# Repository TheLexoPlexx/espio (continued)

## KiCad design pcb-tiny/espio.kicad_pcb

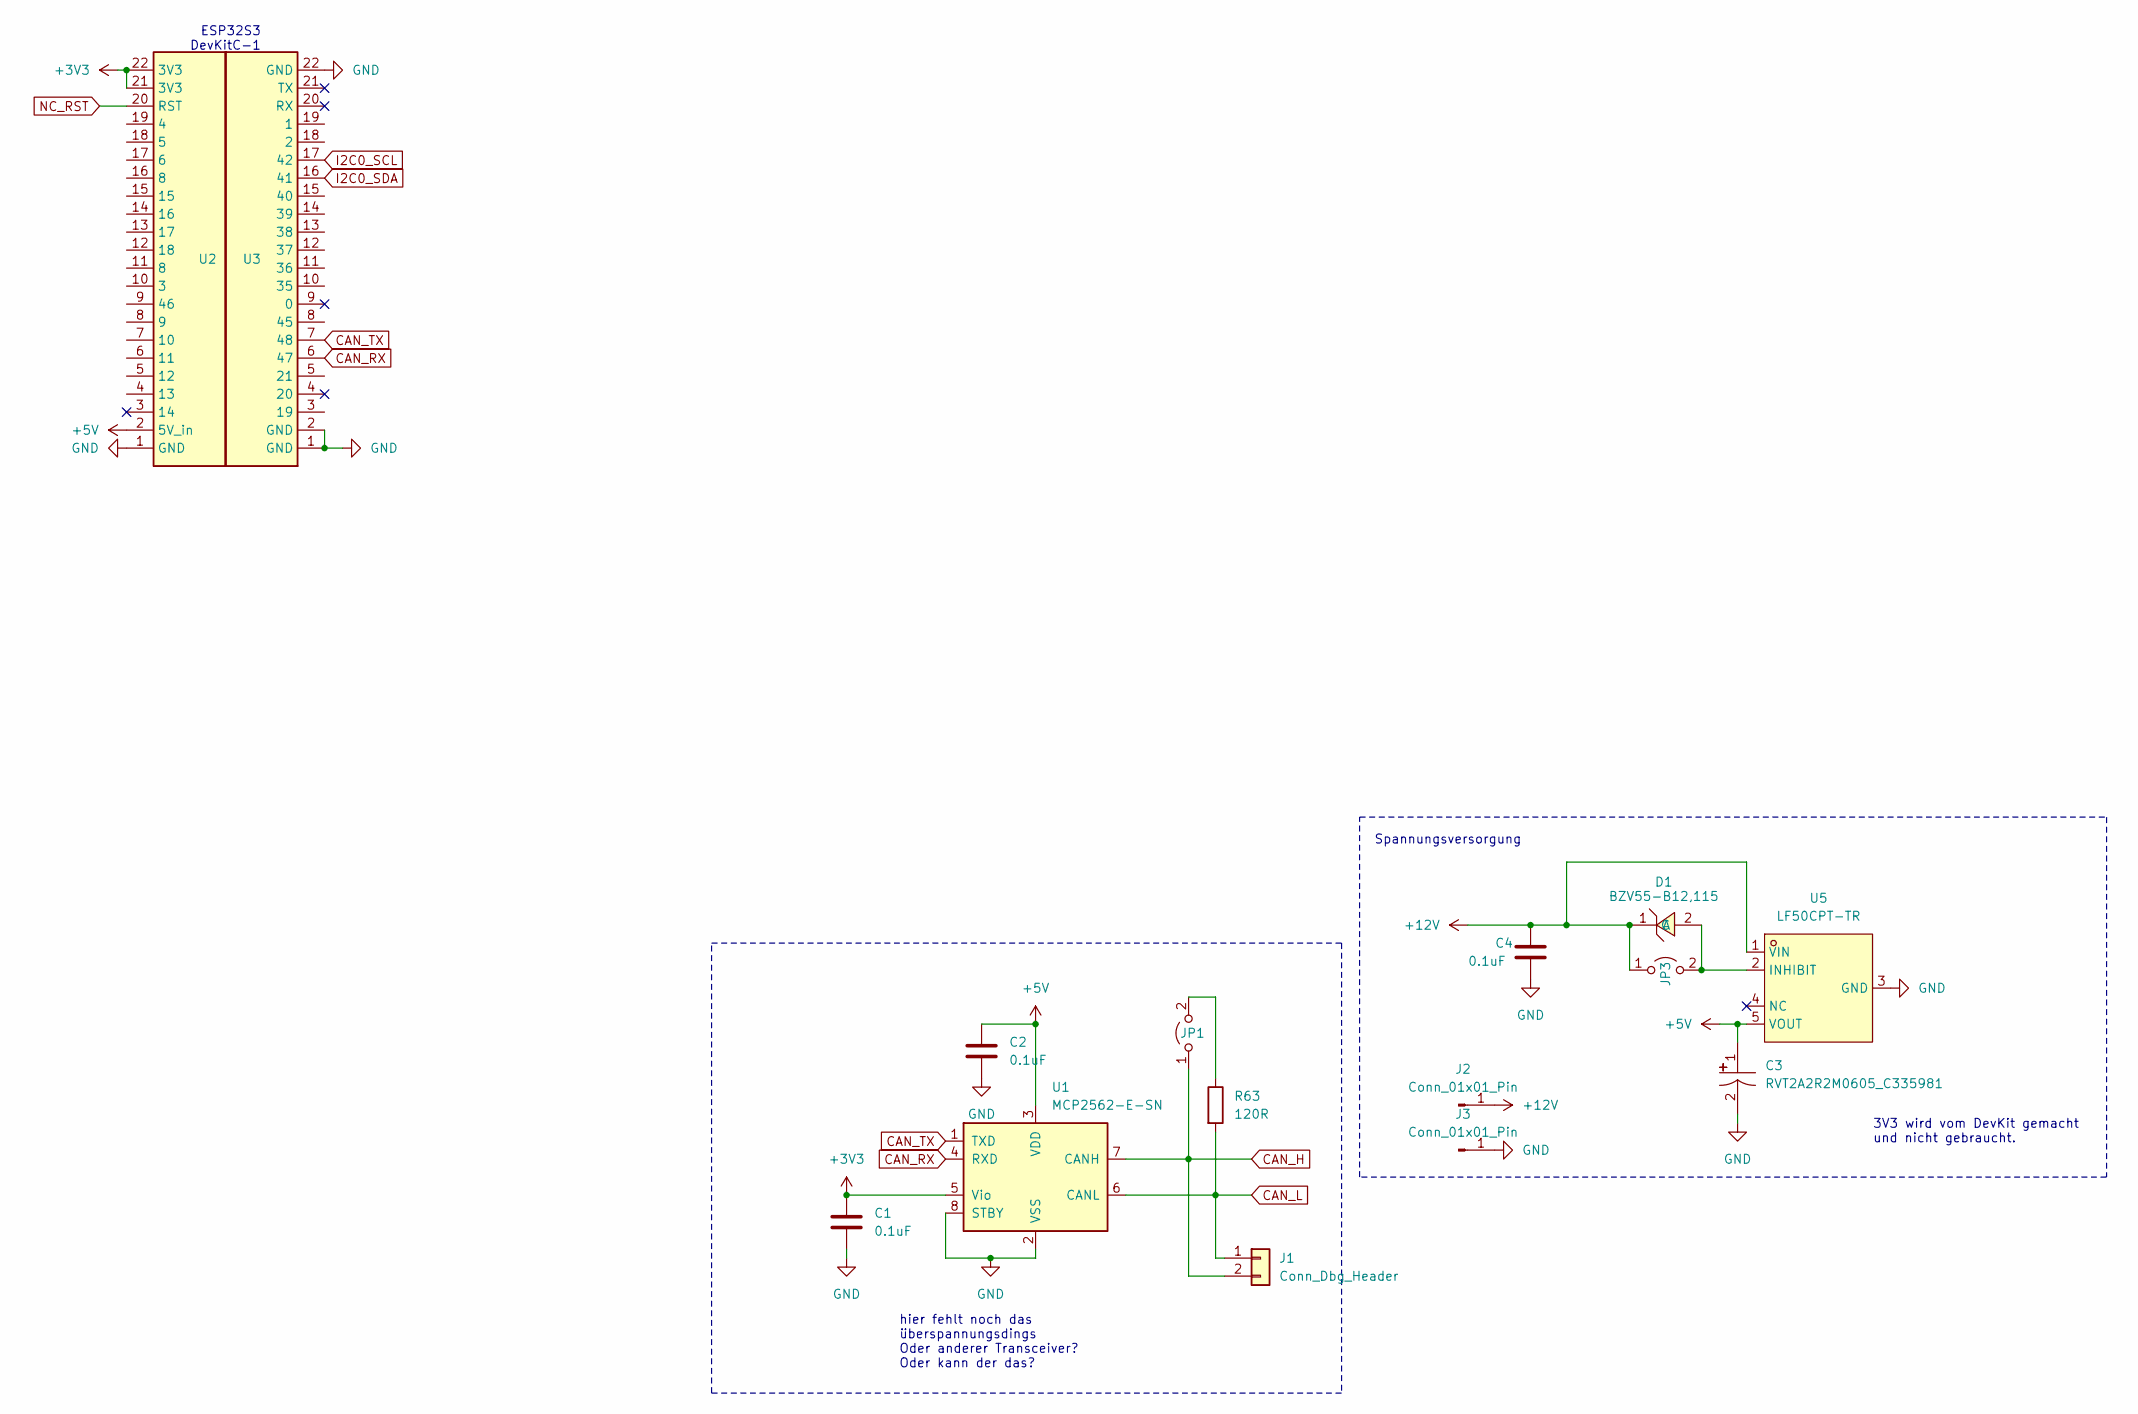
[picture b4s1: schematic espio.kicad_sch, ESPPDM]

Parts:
C1, C2, C4: 0.1uF; C_0603_1608Metric
C3: RVT2A2R2M0605_C335981; CAP-SMD_BD6.3-L6.6-W6.6-FD; LCSC Part C335981
D1: BZV55-B12,115; SOD-80C_L3.3-W1.5-RD; LCSC Part C426807
J1: Conn_Dbg_Header; PinHeader_1x02_P2.54mm_Vertical
J2, J3: Conn_01x01_Pin; SolderWirePad_1x01_SMD_5x10mm
JP1, JP3: Jumper_2_Open; SolderJumper-2_P1.3mm_Open_Pad1.0x1.5mm
R63: 120R; R_0603_1608Metric
U1: MCP2562-E-SN; SOIC-8_3.9x4.9mm_P1.27mm; lcsc C53609
U2, U3: PinSocket_1x22_P2.54mm_Vertical
U5: LF50CPT-TR; PPAK-5_L6.5-W6.1-P1.27-LS10.0-TL; LCSC Part C2970955

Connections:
+3V3: C1.1, U1.5 (Vio), U2.21 (3V3), U2.22 (3V3)
+5V: C2.1, C3.1, U1.3 (VDD), U2.2 (5V_in), U5.5 (VOUT)
+12V: C4.1, D1.1 (C), J2.1, JP3.1 (A), U5.1 (VIN)
CAN_H: J1.2, JP1.1 (A), U1.7 (CANH)
CAN_L: J1.1, R63.2, U1.6 (CANL)
CAN_RX: U1.4 (RXD), U3.6 (47)
CAN_TX: U1.1 (TXD), U3.7 (48)
GND: C1.2, C2.2, C3.2, C4.2, J3.1, U1.2 (VSS), U1.8 (STBY), U2.1 (GND), U3.1 (GND), U3.2 (GND), U3.22 (GND), U5.3 (GND)
I2C0_SCL: U3.17 (42)
I2C0_SDA: U3.16 (41)
NC_RST: U2.20 (RST)
unnamed: D1.2 (A), JP3.2 (B), U5.2 (INHIBIT)
unnamed: JP1.2 (B), R63.1

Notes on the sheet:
3V3 wird vom DevKit gemacht und nicht gebraucht.
hier fehlt noch das überspannungsdings Oder anderer Transceiver? Oder kann der das?
Spannungsversorgung
ESP32S3 DevKitC-1

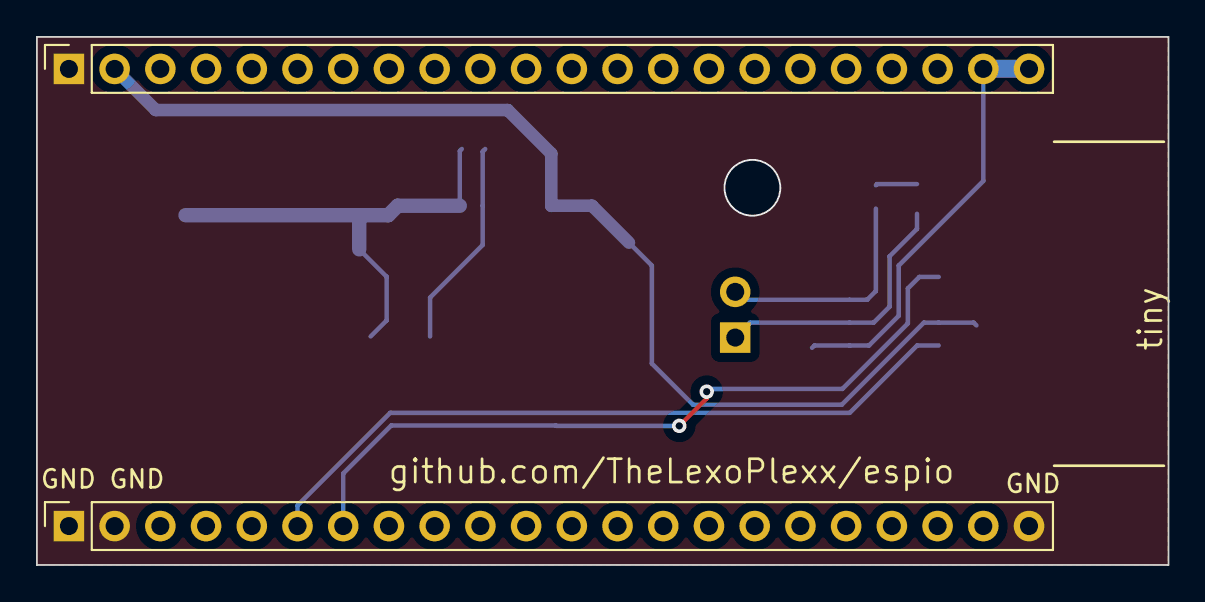
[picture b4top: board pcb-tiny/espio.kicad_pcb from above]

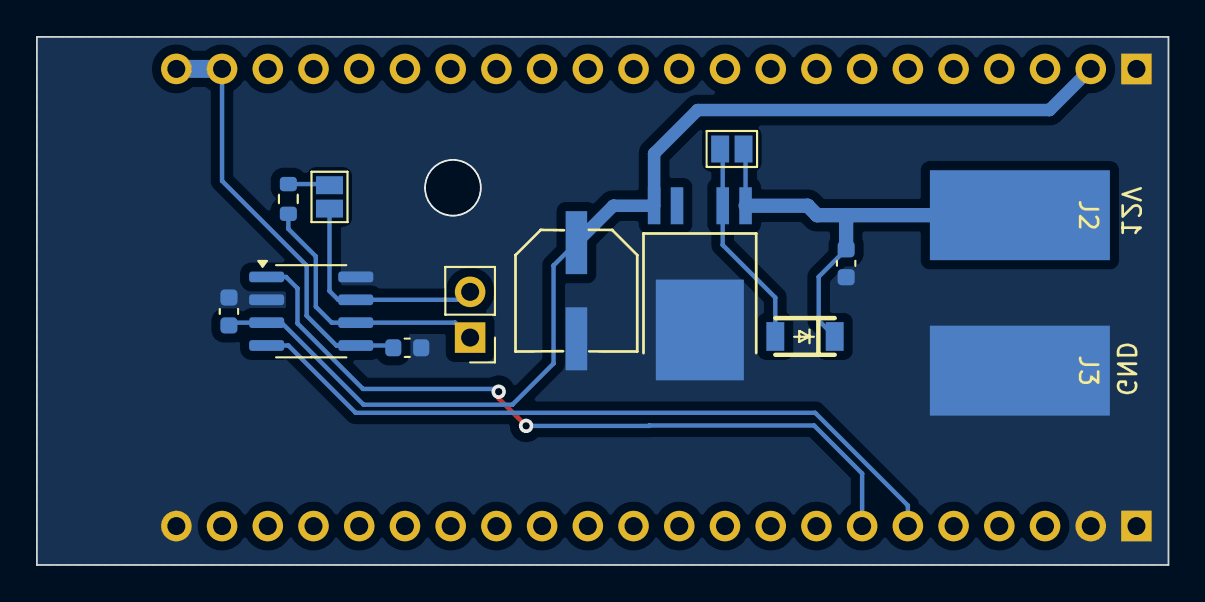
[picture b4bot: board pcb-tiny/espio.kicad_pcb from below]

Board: 2 copper layers, 62.9 x 29.3 mm, 15 parts (13 on the bottom side), 10 nets.

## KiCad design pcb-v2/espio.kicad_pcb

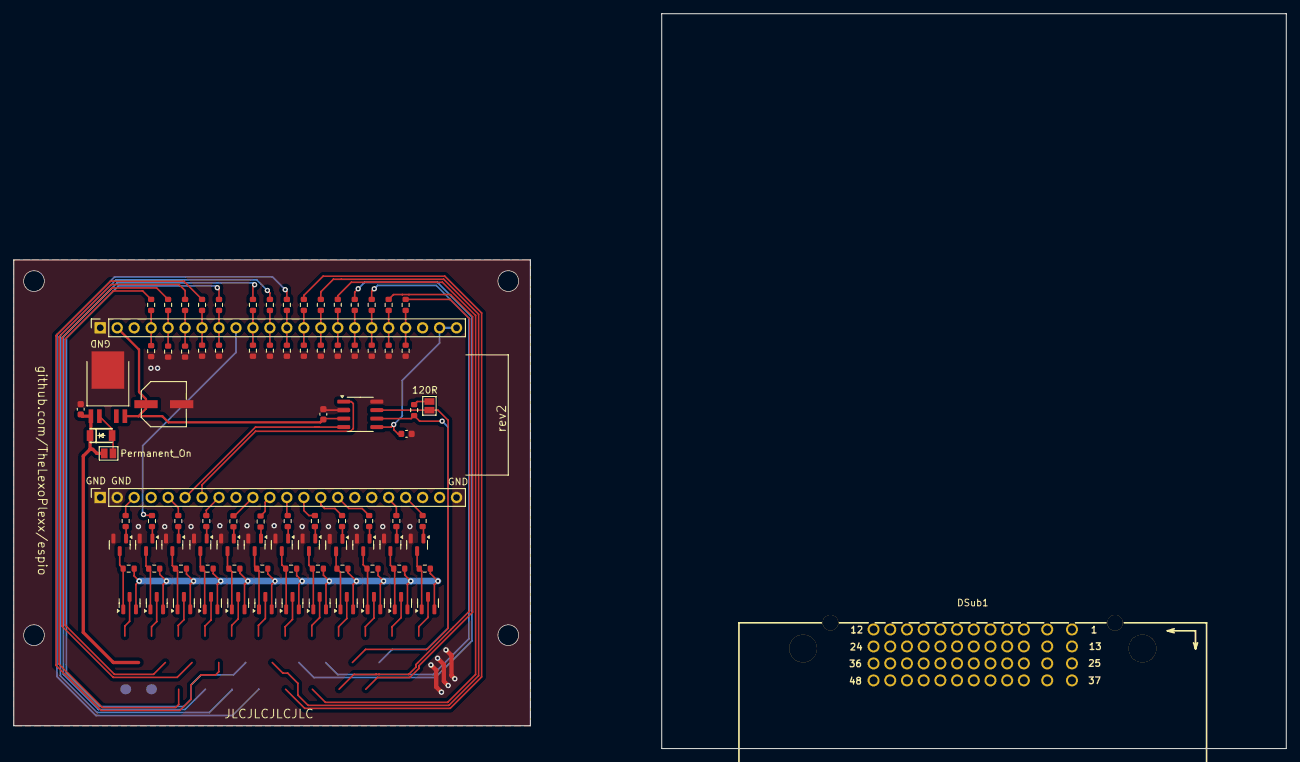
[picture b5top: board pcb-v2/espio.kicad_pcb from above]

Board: 2 copper layers, 77.3 x 69.7 mm, 91 parts (0 on the bottom side), 61 nets.

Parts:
C1, C2, C4: 0.1uF; C_0603_1608Metric
C3: RVT2A2R2M0605_C335981; CAP-SMD_BD6.3-L6.6-W6.6-FD
D1: BZV55-B12,115; SOD-80C_L3.3-W1.5-RD
DSub1: 5007620481; CONN-TH_5007620481
JP1, JP3: Jumper_2_Open; SolderJumper-2_P1.3mm_Open_Pad1.0x1.5mm
Q1, Q3, Q5, Q7, Q9, Q11, Q13, Q15, Q17, Q19, Q21, Q23: BC817; SOT-23
Q2, Q4, Q6, Q8, Q10, Q12, Q14, Q16, Q18, Q20, Q22, Q24: IRLML6402; SOT-23
R1, R18, R19, R20, R21, R22, R23, R24, R25, R26, R27, R28: 100R; R_0603_1608Metric
R13, R16, R34, R36, R38, R40, R42, R44, R46, R48, R50, R52, R54, R56, R58: 6k8; R_0603_1608Metric
R14, R15, R33, R35, R37, R39, R41, R43, R45, R47, R49, R51, R53, R55, R57: 33k; R_0603_1608Metric
R29, R30, R31, R32, R59, R60, R61, R62, R64, R65, R66, R67: 10k; R_0603_1608Metric
R63: 120R; R_0603_1608Metric
U1: MCP2562-E-SN; SOIC-8_3.9x4.9mm_P1.27mm
U2, U3: PinSocket_1x22_P2.54mm_Vertical
U5: LF50CPT-TR; PPAK-5_L6.5-W6.1-P1.27-LS10.0-TL

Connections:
+3V3: C1.1, U1.5 (Vio), U2.21 (3V3), U2.22 (3V3)
+5V: C2.1, C3.1, U1.3 (VDD), U2.2 (5V_in), U5.5 (VOUT)
+12V: C4.1, D1.1 (C), JP3.1 (A), Q2.2 (S), Q4.2 (S), Q6.2 (S), Q8.2 (S), Q10.2 (S), Q12.2 (S), Q14.2 (S), Q16.2 (S), Q18.2 (S), Q20.2 (S), Q22.2 (S), Q24.2 (S), R29.2, R30.2, R31.2, R32.2, R59.2, R60.2, R61.2, R62.2, R64.2, R65.2, R66.2, R67.2, U5.1 (VIN)
/SwitchingNode1/SN_IN: R1.1, U3.19 (1)
/SwitchingNode2/SN_IN: R18.1, U3.18 (2)
/SwitchingNode3/SN_IN: R19.1, U3.15 (40)
/SwitchingNode4/SN_IN: R20.1, U3.14 (39)
/SwitchingNode5/SN_IN: R21.1, U3.13 (38)
/SwitchingNode6/SN_IN: R22.1, U3.12 (37)
/SwitchingNode7/SN_IN: R23.1, U3.11 (36)
/SwitchingNode8/SN_IN: R24.1, U3.10 (35)
/SwitchingNode9/SN_IN: R25.1, U3.8 (45)
/SwitchingNode10/SN_IN: R26.1, U3.5 (21)
/SwitchingNode12/SN_IN: R28.1, U3.3 (19)
CAN_H: JP1.1 (A), U1.7 (CANH)
CAN_L: R63.2, U1.6 (CANL)
CAN_RX: U1.4 (RXD), U3.6 (47)
CAN_TX: U1.1 (TXD), U3.7 (48)
GND: C1.2, C2.2, C3.2, C4.2, Q1.2 (E), Q3.2 (E), Q5.2 (E), Q7.2 (E), Q9.2 (E), Q11.2 (E), Q13.2 (E), Q15.2 (E), Q17.2 (E), Q19.2 (E), Q21.2 (E), Q23.2 (E), R13.2, R16.2, R34.2, R36.2, R38.2, R40.2, R42.2, R44.2, R46.2, R48.2, R50.2, R52.2, R54.2, R56.2, R58.2, U1.2 (VSS), U1.8 (STBY), U2.1 (GND), U3.1 (GND), U3.2 (GND), U3.22 (GND), U5.3 (GND)
unnamed: D1.2 (A), JP3.2 (B), U5.2 (INHIBIT)
unnamed: JP1.2 (B), R63.1
unnamed: Q1.1 (B), R1.2
unnamed: Q1.3 (C), Q2.1 (G), R29.1
unnamed: Q3.1 (B), R18.2
unnamed: Q3.3 (C), Q4.1 (G), R30.1
unnamed: Q5.1 (B), R19.2
unnamed: Q5.3 (C), Q6.1 (G), R31.1
unnamed: Q7.1 (B), R20.2
unnamed: Q7.3 (C), Q8.1 (G), R32.1
unnamed: Q9.1 (B), R21.2
unnamed: Q9.3 (C), Q10.1 (G), R59.1
unnamed: Q11.1 (B), R22.2
unnamed: Q11.3 (C), Q12.1 (G), R60.1
unnamed: Q13.1 (B), R23.2
unnamed: Q13.3 (C), Q14.1 (G), R61.1
unnamed: Q15.1 (B), R24.2
unnamed: Q15.3 (C), Q16.1 (G), R62.1
unnamed: Q17.1 (B), R25.2
unnamed: Q17.3 (C), Q18.1 (G), R64.1
unnamed: Q19.1 (B), R26.2
unnamed: Q19.3 (C), Q20.1 (G), R65.1
unnamed: Q21.1 (B), R27.2
unnamed: Q21.3 (C), Q22.1 (G), R66.1
unnamed: Q23.1 (B), R28.2
unnamed: Q23.3 (C), Q24.1 (G), R67.1
unnamed: R15.2, R16.1, U2.11 (8)
unnamed: R39.2, R40.1, U2.16 (8)
unnamed: R41.2, R42.1, U2.15
unnamed: R13.1, R14.2, U2.10 (3)
unnamed: R33.2, R34.1, U2.19 (4)
unnamed: R35.2, R36.1, U2.18 (5)
unnamed: R37.2, R38.1, U2.17 (6)
unnamed: R57.2, R58.1, U2.8 (9)
unnamed: R55.2, R56.1, U2.7 (10)
unnamed: R53.2, R54.1, U2.6 (11)
unnamed: R51.2, R52.1, U2.5 (12)
unnamed: R49.2, R50.1, U2.4 (13)
unnamed: R43.2, R44.1, U2.14 (16)
unnamed: R45.2, R46.1, U2.13 (17)
unnamed: R47.2, R48.1, U2.12 (18)
OUT_12: R27.1, U2.9 (46)

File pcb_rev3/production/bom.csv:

Designator,Footprint,Quantity,Value,LCSC Part #
"C1, C2, C4",0603,3,0.1uF,
C3,CAP-SMD_BD6.3-L6.6-W6.6-FD,1,RVT2A2R2M0605_C335981,C335981
D1,SOD-80C_L3.3-W1.5-RD,1,"BZV55-B12,115",C426807
J1,PinHeader_1x02_P2.54mm_Vertical,1,Conn_Dbg_Header,
J2,PinSocket_1x07_P2.54mm_Vertical,1,Conn_01x07,
J3,PinSocket_1x08_P2.54mm_Vertical,1,Conn_01x08,
"JP1, JP3",SolderJumper-2_P1.3mm_Open_Pad1.0x1.5mm,2,Jumper_2_Open,
JP2,SolderJumper-2_P1.3mm_Open_Pad1.0x1.5mm,1,VCC_as_Pin_8,
"Q1, Q10, Q11, Q12, Q13, Q14, Q15, Q3, Q5, Q7, Q9",SOT-23,11,BC817,
"Q2, Q4, Q6, Q8",SOT-23,4,IRLML6402,
"R1, R18, R19, R20",0603,4,100R,
"R13, R16, R50, R52, R54, R56, R58",0603,7,6k8,
"R14, R15, R49, R51, R53, R55, R57",0603,7,33k,
"R29, R30, R31, R32",0603,4,10k,
R63,0603,1,120R,
U1,SOIC-8_3.9x4.9mm_P1.27mm,1,MCP2562-E-SN,
"U2, U3",PinSocket_1x22_P2.54mm_Vertical,2,~,
U5,PPAK-5_L6.5-W6.1-P1.27-LS10.0-TL,1,LF50CPT-TR,C2970955
U6,CONN-TH_35P-P4.00_K776180WR-2,1,K776180WR-1,C2997462

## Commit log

2025-03-07 Rev2
2025-03-07 gitignore
2025-03-09 Pre MCPWM
2025-06-18 working
2025-06-19 feiertag
2025-06-23 some stuff
2025-06-24 Fixed urls
2025-06-26 Donnerstag
2025-06-26 Donnerstag2
2025-06-28 Add counters to ebu, update schematic
2025-07-04 safety commit
2025-07-06 up to date
2025-07-06 forgot gitignore
2025-07-06 add gitignore
2025-07-20 edited a lot
2025-07-20 removed comment
2025-07-23 Final stretch, maybe
2025-07-24 Edit schematic
2025-07-26 Fixed brake pedal status pin
2025-07-26 add lock
2025-07-27 Refactor dev_can_sender and fix some things
2025-07-27 edit some stuff at ebu/can
2025-07-27 Fixed KOMBI
2025-07-27 Edit engine_bay_unit and main
2025-07-27 Fixed lots of stuff but refactoring is desperatly needed
2025-07-27 Sonntag
2025-07-27 Sonntag2
2025-07-27 Brake pedal does not work as expected when ignition is on
2025-07-29 pin fixes
2025-07-29 pcb v3
2025-08-01 FIXED
2025-08-01 Can-Thread-Split
2025-08-01 pirates
2025-08-01 idk if this works
2025-08-01 works but not beautiful
2025-08-02 Huge refactor (by Gemini) to only use two threads. - one for can receive - one for the main app logic Doesn't need AppState anymore. Added filter to can-config.
2025-08-02 should be working now
2025-08-04 Fried
2025-08-04 logging
2025-08-15 Added ESPIO struct and ESPIO pins, but not sure if I like it.
2025-08-16 rgb_led_fix 1
2025-08-16 Seemingly fixed the LED issue.
2025-08-16 recovered lost pcb
2025-08-16 fixed the dumb schematic
2025-08-16 learned from my mistakes
2025-08-17 added some diodes, fuses etc
2025-08-17 surface
2025-08-18 major work
2025-08-18 added missing pieces
2025-08-19 dienstag
2025-08-19 edit pulldown
2025-08-19 edit gitingore
2025-10-19 Engine_bay_unit turns on external LED for whatever reason
2025-10-19 Refactor, fix external LED conflict
